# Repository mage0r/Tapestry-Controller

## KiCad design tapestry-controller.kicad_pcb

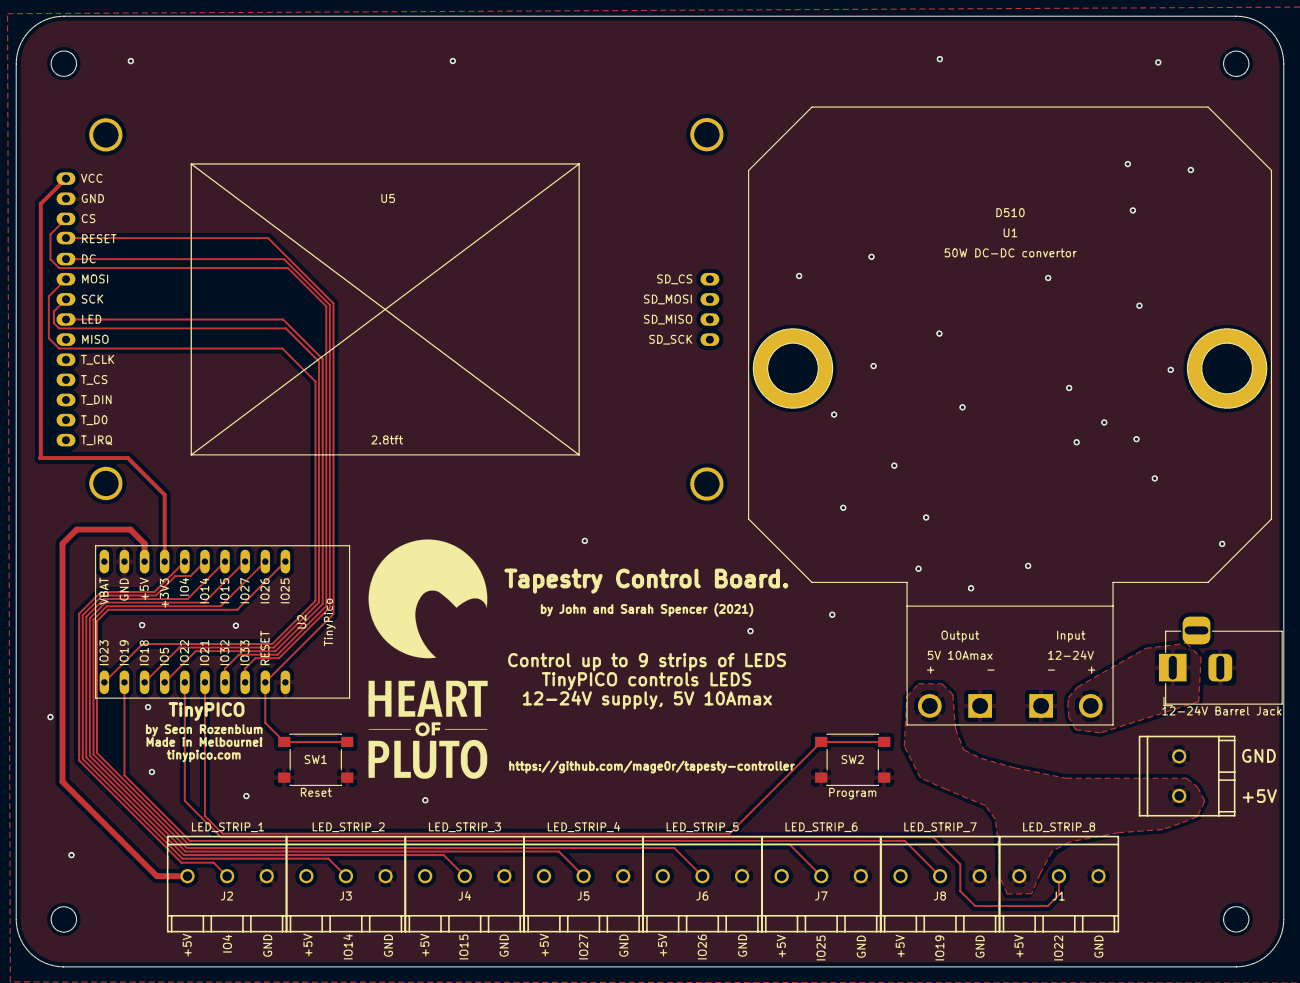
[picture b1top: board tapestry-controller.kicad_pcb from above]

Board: 2 copper layers, 160.0 x 120.0 mm, 20 parts (0 on the bottom side), 18 nets.

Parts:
H1, H2, H3, H4: MountingHole; MountingHole_3.2mm_M3
J1: LED_STRIP_8; p2035a-dinkle-3-way-5mm
J2: LED_STRIP_1; p2035a-dinkle-3-way-5mm
J3: LED_STRIP_2; p2035a-dinkle-3-way-5mm
J4: LED_STRIP_3; p2035a-dinkle-3-way-5mm
J5: LED_STRIP_4; p2035a-dinkle-3-way-5mm
J6: LED_STRIP_5; p2035a-dinkle-3-way-5mm
J7: LED_STRIP_6; p2035a-dinkle-3-way-5mm
J8: LED_STRIP_7; p2035a-dinkle-3-way-5mm
J11: 12-24V Barrel Jack; BarrelJack_Horizontal
J12: +5V; p2034a-dinkle-2-way-5mm
SW1: Reset; SW_Push_1P1T_NO_6x6mm_H9.5mm
SW2: Program; SW_Push_1P1T_NO_6x6mm_H9.5mm
U1: D510; daygreen-d510
U2: TinyPico
U4: HoP_Logo; HoP_logo_large
U5: 2.8tft; SPI_Screen_320_x_240_2.8

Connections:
+3V3: U2.7, U5.1
+5V: J1.1, J2.1, J3.1, J4.1, J5.1, J6.1, J7.1, J8.1, J12.1, U1.1, U2.8
+24V: J11.1, U1.4
/CS_Disp: U2.17, U5.3
/DC: U2.18, U5.5
/IO4: J2.2, U2.6
/IO14: J3.2, U2.5
/IO15: J4.2, U2.4
/IO18: U2.13, U5.7
/IO19: J8.2, U2.12
/IO21: SW2.2, U2.16
/IO22: J1.2, U2.15
/IO23: U2.11, U5.6
/IO25: J7.2, U2.1
/IO26: J6.2, U2.2
/IO27: J5.2, U2.3
/RESET: SW1.2, U2.19, U5.4
GND: J1.3, J2.3, J3.3, J4.3, J5.3, J6.3, J7.3, J8.3, J11.2, J12.2, SW1.1, SW2.1, U1.2, U1.3, U2.9, U2.20, U5.2

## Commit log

2021-10-14 :tada: Added .gitattributes & .gitignore files
2021-10-14 Initial upload
    I may have forgotten about this one for a while, so the initial upload
    actually represents version 2.0 of this board.
2021-10-27 Updated to fix the upside down LCD
2021-10-27 cleanup and adding photos
2023-12-30 Final Release Version
